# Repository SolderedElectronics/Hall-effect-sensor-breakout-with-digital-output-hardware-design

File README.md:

# Hall effect sensor breakout with digital output Hardware Design

## About the Product

|  |
| :----------------------------------------------------------: |
| [Buy Hall effect sensor breakout with digital output](https://www.solde.red/333080) |

The hall effect sensor (Hall Effect sensor) will be able to detect the magnetic field in its vicinity thanks to the aforementioned physical law. A magnetic field that can be created by a magnet, a current flowing through a conductor or some third source, the Hall effect sensor will recognize each. This sensor has a programmed threshold at which it will change the state of its output signal, so it is a sensor with a digital output.

---

## Repository Contents

This repository contains all design files for Hall effect sensor breakout with digital output, organized as follows:

- **`CAD` folder**: Contains KiCAD design files, including:
  - Schematics
  - PCB layout
  - Panel PCB layout
  - Source 3D files in Fusion360, if any
  - All files are sorted by version with a detailed change log.
- **`OUTPUTS` folder**: Includes all production-ready files, such as:
  - Bill of Materials (BOM) and interactive BOM (iBOM)
  - PDF versions of schematics
  - 3D `.step` file of the board
  - 3D-printable models
  - Gerber files for PCB manufacturing
  - Image of the pinout of the board
  - Product image
  - Compliance, legal and generic sales documents

Refer to the `Change Log` in the CAD folder for details about updates between versions.

---

## Learn More About the Product

Beyond the repository, explore the following resources:

### Soldered Verify

The **Soldered Verify** system ensures every board you purchase from Soldered is fully functional. It also provides access to exclusive test data for your product. To get started, find the unique Soldered Verify ID on your product's packaging and enter the ID on the [Soldered Verify page](https://soldered.com/verify/) to access test results and additional product details.

### Soldered Community

Soldered Community is your go-to place for technical support. Our engineers track and answer all questions posted there, and it’s a great space for the maker community. Get answers to your questions and solutions for your challenges at [Soldered Community](https://soldered.com/community).

### solde.red

solde.red is an ultimate URL shortener and information hub. Access it by typing solde.red/ followed by your product SKU, e.g., [solde.red/333000](https://solde.red/333000), to find getting-started guides, datasheets, open-source hardware and software files, certifications, images, pinouts, and more. Read more about the shortener [here](https://solde.red/info/).

---

## Contributing

Contributions are welcome! Here’s how you can get involved:

- Submit pull requests to enhance the design or fix issues.
- Report bugs or problems by opening an issue.

We encourage community collaboration to make this product even better.

---

## About Soldered

[Soldered for Makers](https://soldered.com) specializes in designing and manufacturing electronic products tailored for enthusiasts, ranging from hobbyists to professionals. Our portfolio includes electronic boards, sensors, and actuators that are widely utilized in fields such as microelectronics, mechatronics, robotics, programming, and IoT. Every product we offer is designed in-house and built upon open-source hardware and software platforms. Proudly certified and manufactured within the European Union, our catalog likely includes the product you need for your project.

We complement these products with comprehensive tutorials and manuals, product descriptions, schematics, programming codes, and project examples. Our round-the-clock [customer and technical support](https://soldered.com/community) is available for all our products, irrespective of the sales channel. Soldered’s success and services reflect our maker community’s unwavering [trust](https://www.trustpilot.com/review/soldered.com), for which we are deeply grateful. Join our community and create using Soldered products.

---

## License

All Soldered open-source hardware (OSH) is under The TAPR Open Hardware License. Read more in the LICENSE file located in this repository.

**Disclaimer:**

No warranty - all designs in this repository are distributed in the hope that they will be useful, but without any warranty. They are provided "AS IS", therefore without warranty of any kind, either expressed or implied. The entire quality and performance of what you do with the contents of this repository are your responsibility. In no event Soldered Electronics will be liable for your damages, or losses, including any general, special, incidental, or consequential damage arising out of the use or inability to use the contents of this repository. 

---

## Have fun!

Thank you for your support from your fellow makers at Soldered Electronics.

Happy Making!

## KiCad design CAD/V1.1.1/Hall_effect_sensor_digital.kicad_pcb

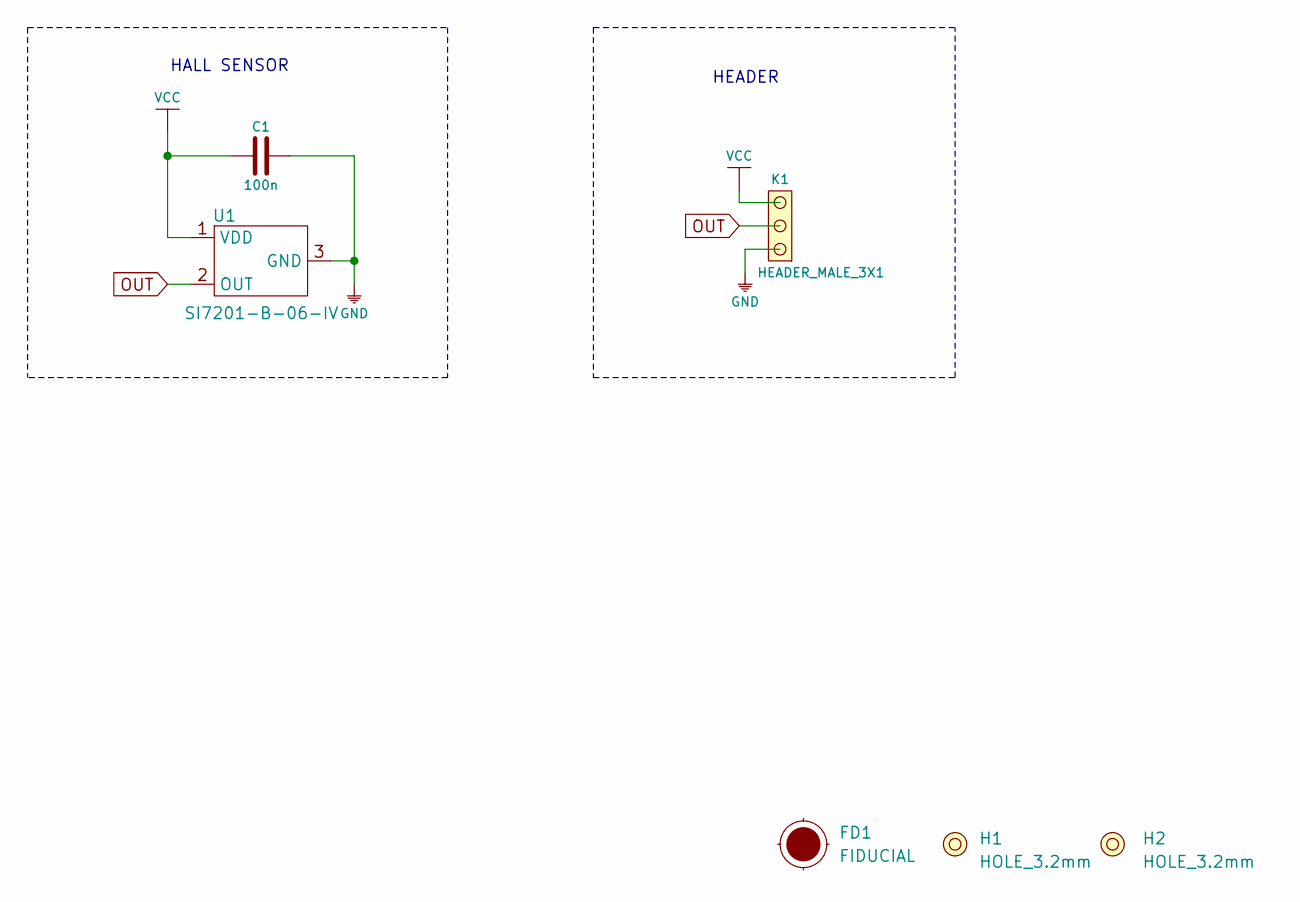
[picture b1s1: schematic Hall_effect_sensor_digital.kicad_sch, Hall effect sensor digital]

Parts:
C1: 100n; 0603C
FD1: FIDUCIAL; FIDUCIAL_23
H1, H2: HOLE_3.2mm
K1: HEADER_MALE_3X1
U1: SI7201-B-06-IV; SOT-23-3

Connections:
GND: C1.2, K1.1, U1.3 (GND)
OUT: K1.2, U1.2 (OUT)
VCC: C1.1, K1.3, U1.1 (VDD)

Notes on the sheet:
HALL SENSOR
HEADER

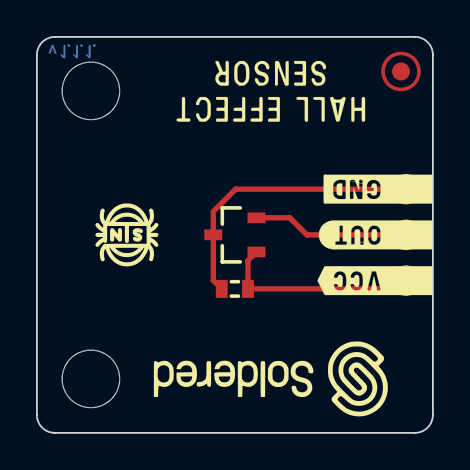
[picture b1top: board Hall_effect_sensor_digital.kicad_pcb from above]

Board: 2 copper layers, 22.0 x 22.0 mm, 6 parts (1 on the bottom side), 3 nets.

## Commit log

2022-08-06 Updating open source files.
